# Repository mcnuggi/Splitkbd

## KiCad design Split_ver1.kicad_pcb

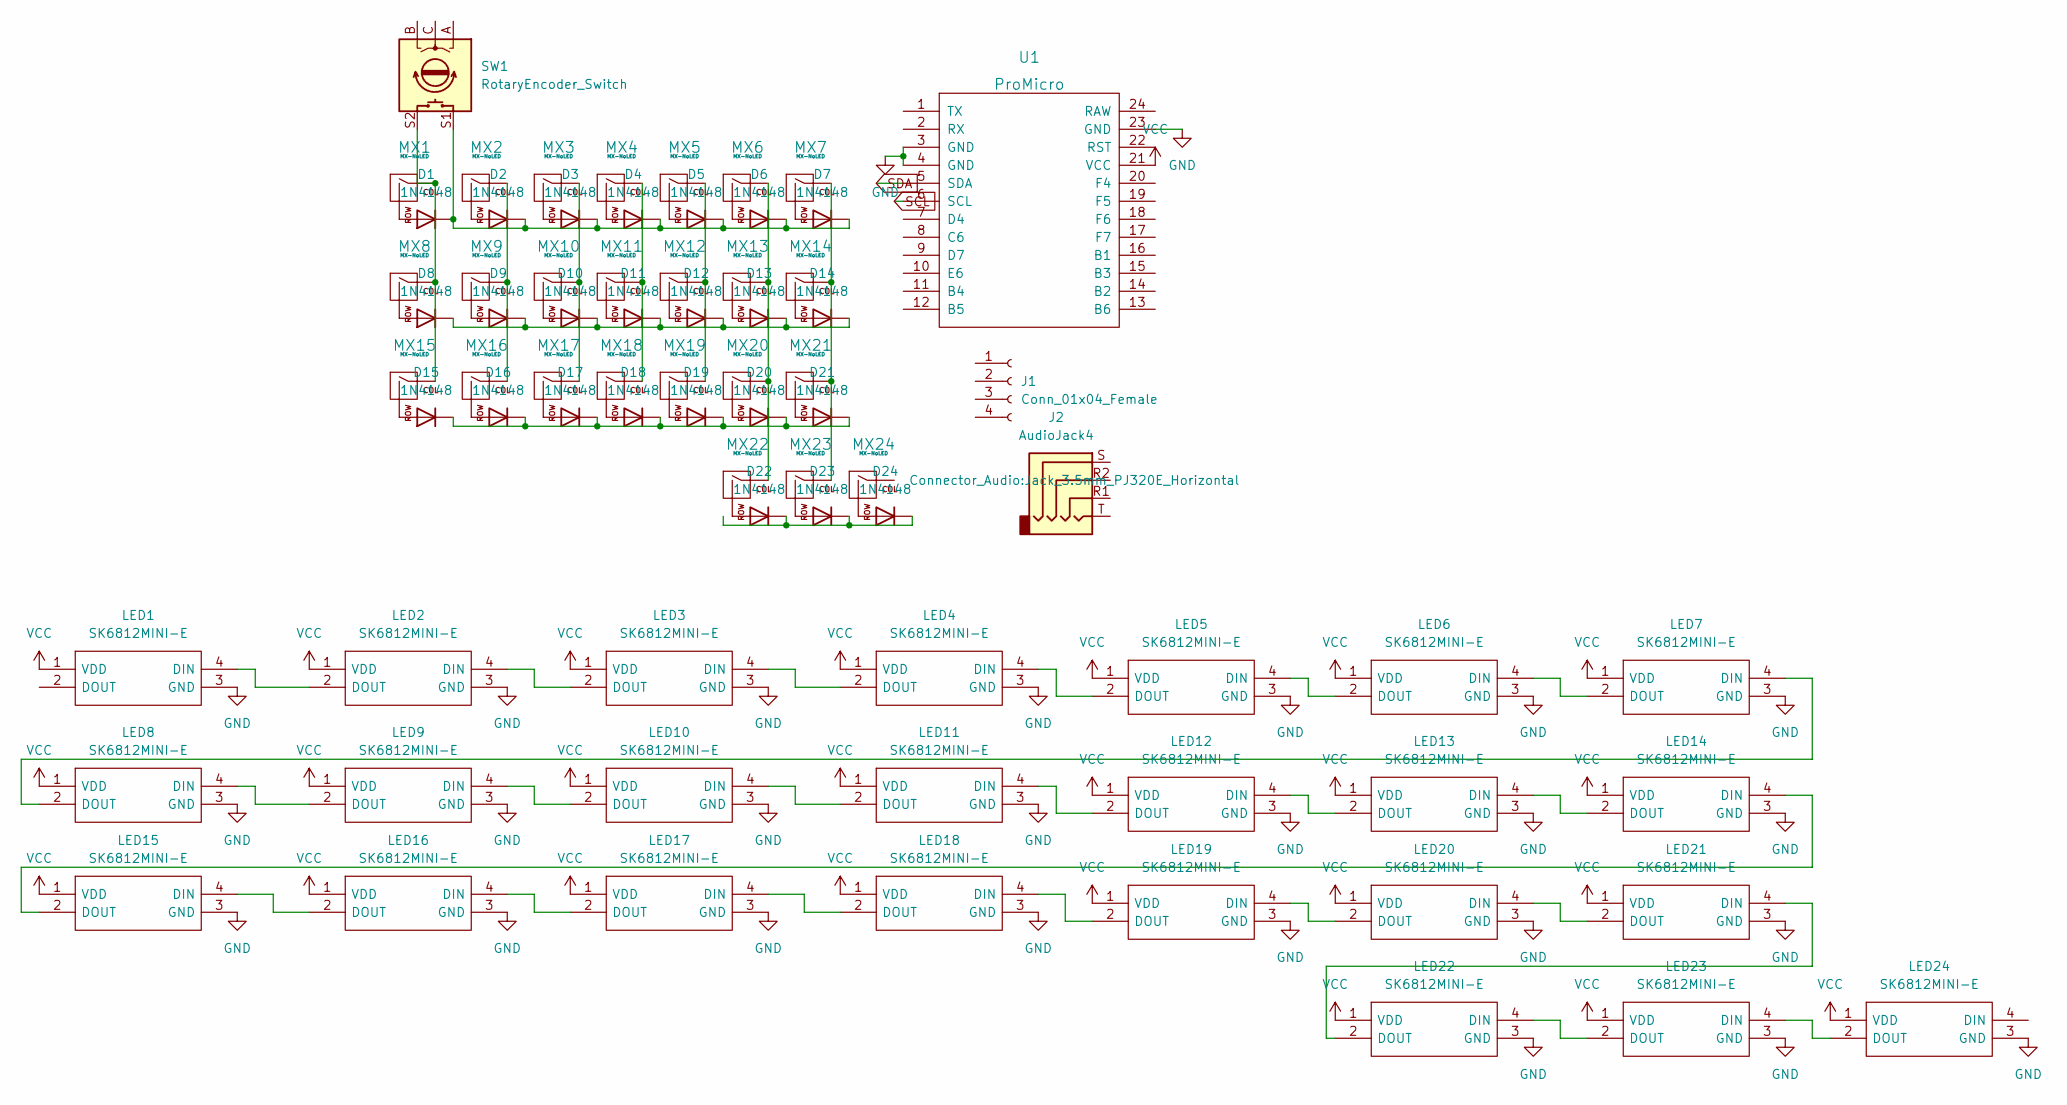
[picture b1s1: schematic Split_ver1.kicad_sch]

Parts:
D1, D2, D3, D4, D5, D6, D7, D8, D9, D10, D11, D12, D13, D14, D15, D16, D17, D18, D19, D20, D21, D22, D23, D24: 1N4148; D_DO-35_SOD27_P7.62mm_Horizontal
J1: Conn_01x04_Female; PinHeader_1x04_P2.54mm_Vertical
J2: AudioJack4; Jack_3.5mm_PJ320E_Horizontal
LED1, LED2, LED3, LED4, LED5, LED6, LED7, LED8, LED9, LED10, LED11, LED12, LED13, LED14, LED15, LED16, LED17, LED18, LED19, LED20, LED21, LED22, LED23, LED24: SK6812MINI-E; Manufacturer_Part_Number SK6812MINI-E
MX1, MX2, MX3, MX4, MX5, MX6, MX7, MX8, MX9, MX10, MX11, MX12, MX13, MX14, MX15, MX16, MX17, MX18, MX19, MX20, MX21, MX22, MX23, MX24: MX-NoLED; SW_Cherry_MX_1.00u_PCB
SW1: RotaryEncoder_Switch; RotaryEncoder_Alps_EC11E-Switch_Vertical_H20mm
U1: ProMicro; ProMicro_1

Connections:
GND: LED1.3 (GND), LED2.3 (GND), LED3.3 (GND), LED4.3 (GND), LED5.3 (GND), LED6.3 (GND), LED7.3 (GND), LED8.3 (GND), LED9.3 (GND), LED10.3 (GND), LED11.3 (GND), LED12.3 (GND), LED13.3 (GND), LED14.3 (GND), LED15.3 (GND), LED16.3 (GND), LED17.3 (GND), LED18.3 (GND), LED19.3 (GND), LED20.3 (GND), LED21.3 (GND), LED22.3 (GND), LED23.3 (GND), LED24.3 (GND), U1.3 (GND), U1.4 (GND), U1.23 (GND)
unnamed: D1.1 (K), D2.1 (K), D3.1 (K), D4.1 (K), D5.1 (K), D6.1 (K), D7.1 (K), SW1.S1
unnamed: D1.2 (A), MX1.2 (ROW)
unnamed: D2.2 (A), MX2.2 (ROW)
unnamed: D3.2 (A), MX3.2 (ROW)
unnamed: D4.2 (A), MX4.2 (ROW)
unnamed: D5.2 (A), MX5.2 (ROW)
unnamed: D6.2 (A), MX6.2 (ROW)
unnamed: D7.2 (A), MX7.2 (ROW)
unnamed: D8.2 (A), MX8.2 (ROW)
unnamed: D9.2 (A), MX9.2 (ROW)
unnamed: D8.1 (K), D9.1 (K), D10.1 (K), D11.1 (K), D12.1 (K), D13.1 (K), D14.1 (K)
unnamed: D10.2 (A), MX10.2 (ROW)
unnamed: D11.2 (A), MX11.2 (ROW)
unnamed: D12.2 (A), MX12.2 (ROW)
unnamed: D13.2 (A), MX13.2 (ROW)
unnamed: D14.2 (A), MX14.2 (ROW)
unnamed: D15.1 (K), D16.1 (K), D17.1 (K), D18.1 (K), D19.1 (K), D20.1 (K), D21.1 (K)
unnamed: D15.2 (A), MX15.2 (ROW)
unnamed: D16.2 (A), MX16.2 (ROW)
unnamed: D17.2 (A), MX17.2 (ROW)
unnamed: D18.2 (A), MX18.2 (ROW)
unnamed: D19.2 (A), MX19.2 (ROW)
unnamed: D20.2 (A), MX20.2 (ROW)
unnamed: D21.2 (A), MX21.2 (ROW)
unnamed: D22.1 (K), D23.1 (K), D24.1 (K)
unnamed: D22.2 (A), MX22.2 (ROW)
unnamed: D23.2 (A), MX23.2 (ROW)
unnamed: D24.2 (A), MX24.2 (ROW)
unnamed: LED1.4 (DIN), LED2.2 (DOUT)
unnamed: LED2.4 (DIN), LED3.2 (DOUT)
unnamed: LED3.4 (DIN), LED4.2 (DOUT)
unnamed: LED4.4 (DIN), LED5.2 (DOUT)
unnamed: LED5.4 (DIN), LED6.2 (DOUT)
unnamed: LED6.4 (DIN), LED7.2 (DOUT)
unnamed: LED7.4 (DIN), LED8.2 (DOUT)
unnamed: LED8.4 (DIN), LED9.2 (DOUT)
unnamed: LED9.4 (DIN), LED10.2 (DOUT)
unnamed: LED10.4 (DIN), LED11.2 (DOUT)
unnamed: LED11.4 (DIN), LED12.2 (DOUT)
unnamed: LED12.4 (DIN), LED13.2 (DOUT)
unnamed: LED13.4 (DIN), LED14.2 (DOUT)
unnamed: LED14.4 (DIN), LED15.2 (DOUT)
unnamed: LED15.4 (DIN), LED16.2 (DOUT)
unnamed: LED16.4 (DIN), LED17.2 (DOUT)
unnamed: LED17.4 (DIN), LED18.2 (DOUT)
unnamed: LED18.4 (DIN), LED19.2 (DOUT)
unnamed: LED19.4 (DIN), LED20.2 (DOUT)
unnamed: LED20.4 (DIN), LED21.2 (DOUT)
unnamed: LED21.4 (DIN), LED22.2 (DOUT)
unnamed: LED22.4 (DIN), LED23.2 (DOUT)
unnamed: LED23.4 (DIN), LED24.2 (DOUT)
unnamed: MX1.1 (COL), MX8.1 (COL), MX15.1 (COL), SW1.S2
unnamed: MX3.1 (COL), MX10.1 (COL), MX17.1 (COL)
unnamed: MX4.1 (COL), MX11.1 (COL), MX18.1 (COL)
unnamed: MX5.1 (COL), MX12.1 (COL), MX19.1 (COL)
unnamed: MX6.1 (COL), MX13.1 (COL), MX20.1 (COL), MX22.1 (COL)
unnamed: MX7.1 (COL), MX14.1 (COL), MX21.1 (COL), MX23.1 (COL)
unnamed: MX2.1 (COL), MX9.1 (COL), MX16.1 (COL)
SCL: U1.6 (SCL)
SDA: U1.5 (SDA)
VCC: LED1.1 (VDD), LED2.1 (VDD), LED3.1 (VDD), LED4.1 (VDD), LED5.1 (VDD), LED6.1 (VDD), LED7.1 (VDD), LED8.1 (VDD), LED9.1 (VDD), LED10.1 (VDD), LED11.1 (VDD), LED12.1 (VDD), LED13.1 (VDD), LED14.1 (VDD), LED15.1 (VDD), LED16.1 (VDD), LED17.1 (VDD), LED18.1 (VDD), LED19.1 (VDD), LED20.1 (VDD), LED21.1 (VDD), LED22.1 (VDD), LED23.1 (VDD), LED24.1 (VDD), U1.21 (VCC)

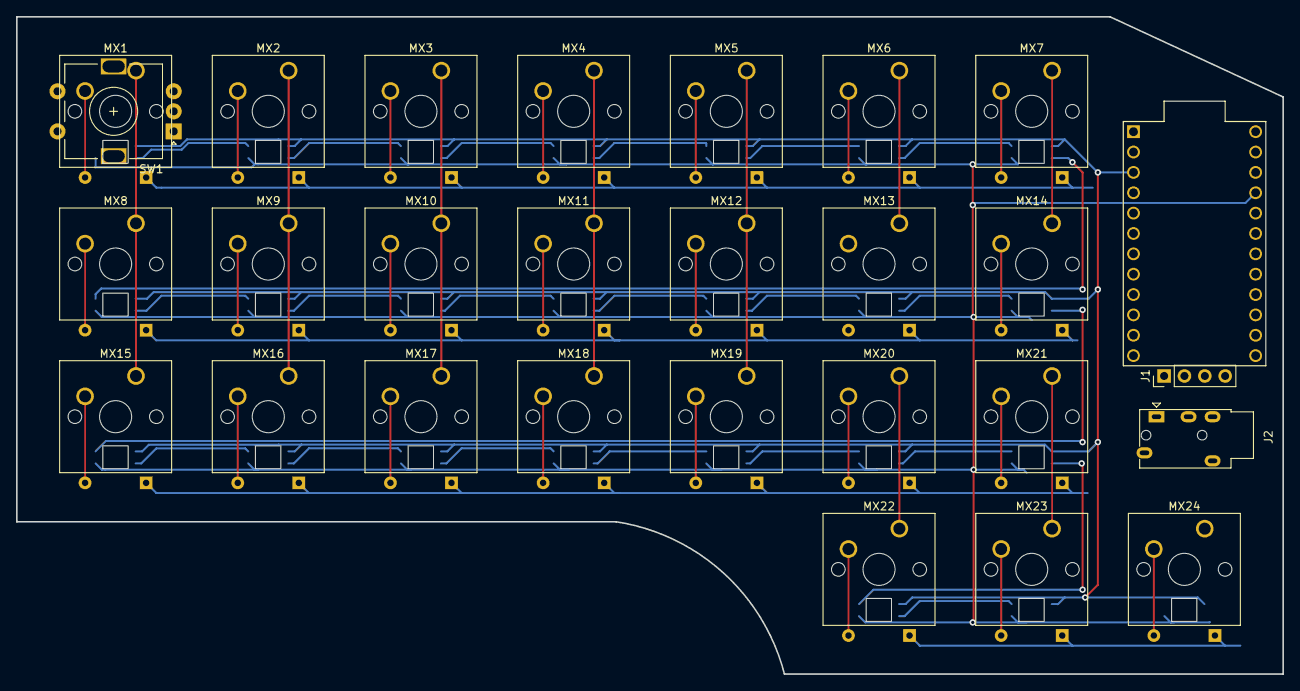
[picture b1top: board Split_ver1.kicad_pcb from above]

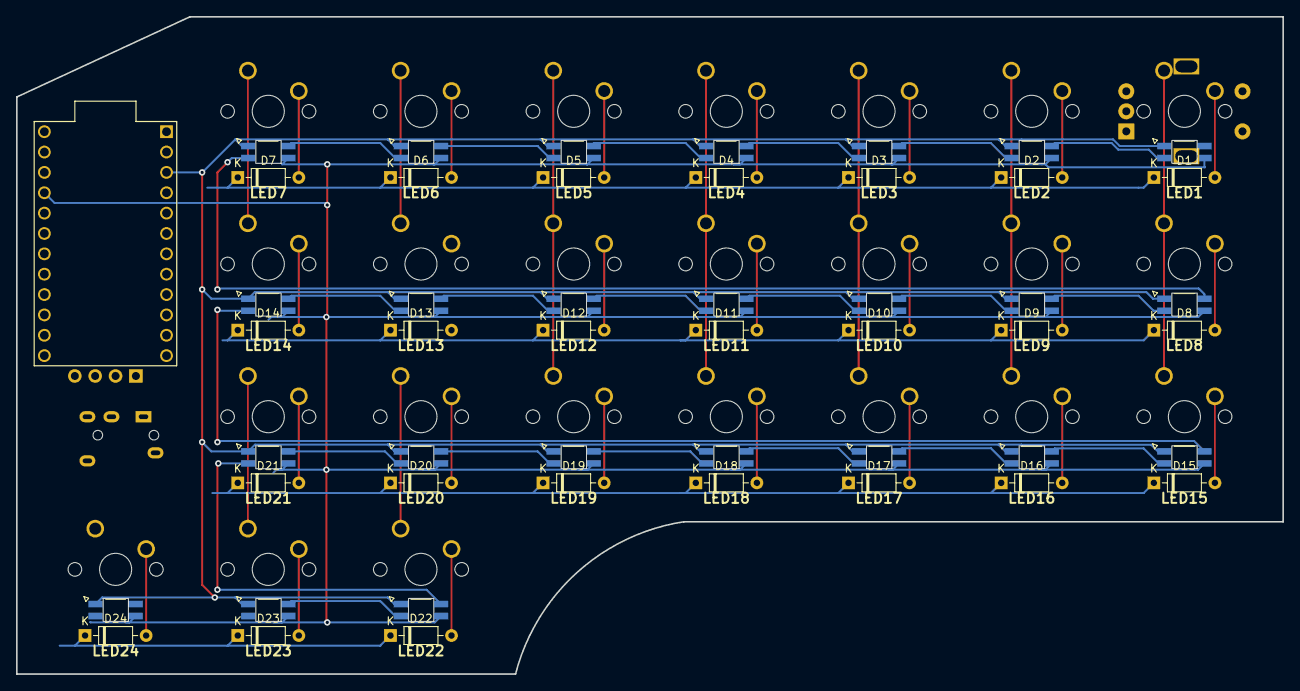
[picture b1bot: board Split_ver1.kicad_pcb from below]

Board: 2 copper layers, 158.0 x 82.0 mm, 76 parts (48 on the bottom side), 60 nets.

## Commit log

2023-04-01 Create parts library
2023-04-01 Create test
